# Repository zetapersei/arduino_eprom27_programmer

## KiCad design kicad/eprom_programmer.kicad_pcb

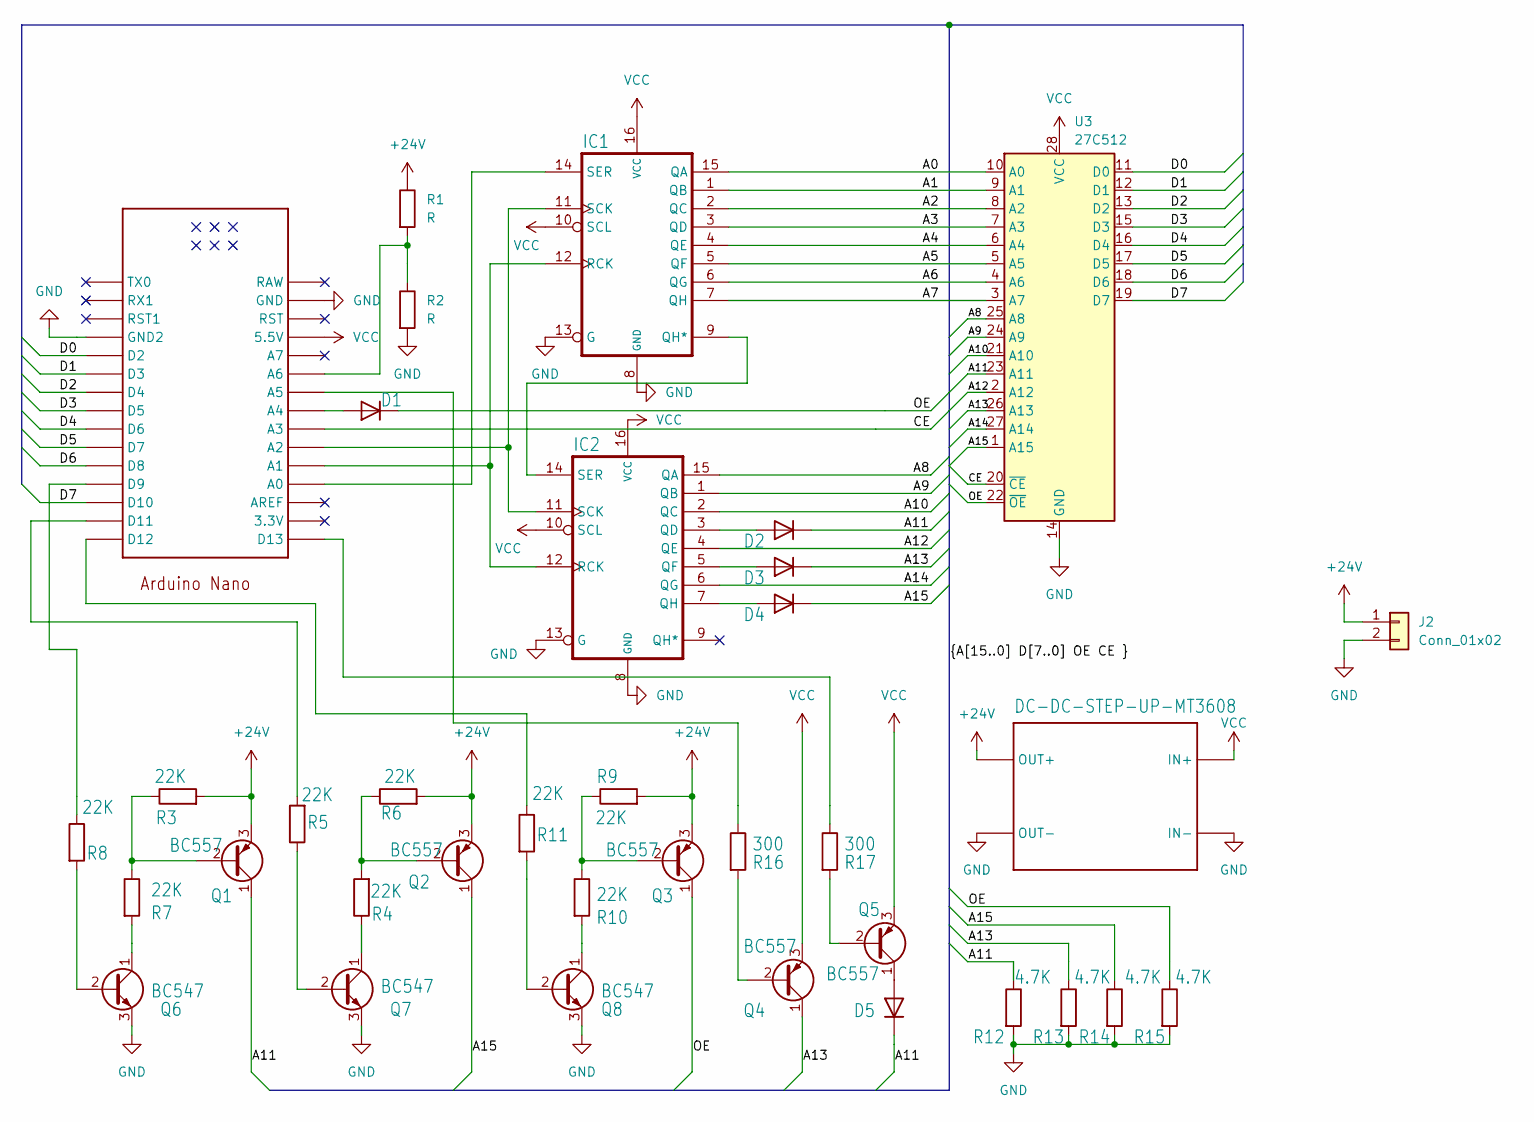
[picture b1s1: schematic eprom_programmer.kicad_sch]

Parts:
D1, D2, D3, D4, D5: 1N4148; D_DO-35_SOD27_P7.62mm_Horizontal
IC1: 74HC595D; DIP-16_W7.62mm_LongPads
IC2: 74595D; DIP-16_W7.62mm_LongPads
J2: Conn_01x02; PinHeader_1x02_P2.54mm_Vertical
Q1, Q2, Q3, Q4, Q5: BC557; TO-92_Inline
Q6, Q7, Q8: BC547; TO-92_Inline
R1, R2: R; R_Axial_DIN0207_L6.3mm_D2.5mm_P10.16mm_Horizontal
R3, R4, R5, R6, R7, R8, R9, R10, R11: 22K; R_Axial_DIN0207_L6.3mm_D2.5mm_P10.16mm_Horizontal
R12, R13, R14, R15: 4.7K; R_Axial_DIN0207_L6.3mm_D2.5mm_P10.16mm_Horizontal
R16, R17: 300; R_Axial_DIN0207_L6.3mm_D2.5mm_P10.16mm_Horizontal
U1: NANO
U2: DC-DC-STEP-UP-MT3608; MT3608
U3: 27C512; DIP_Socket-28_W11.9_W12.7_W15.24_W17.78_W18.5_3M_228-1277-0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

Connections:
+24V: J2.1, Q1.3 (E), Q2.3 (E), Q3.3 (E), R1.1, R3.2, R6.2, R9.2, U2.OUT+
/A0: IC1.15 (QA), U3.10 (A0)
/A1: IC1.1 (QB), U3.9 (A1)
/A2: IC1.2 (QC), U3.8 (A2)
/A3: IC1.3 (QD), U3.7 (A3)
/A4: IC1.4 (QE), U3.6 (A4)
/A5: IC1.5 (QF), U3.5 (A5)
/A6: IC1.6 (QG), U3.4 (A6)
/A7: IC1.7 (QH), U3.3 (A7)
/A8: IC2.15 (QA), U3.25 (A8)
/A9: IC2.1 (QB), U3.24 (A9)
/A10: IC2.2 (QC), U3.21 (A10)
/A11: D2.1 (K), D5.1 (K), Q1.1 (C), R12.1, U3.23 (A11)
/A12: IC2.4 (QE), U3.2 (A12)
/A13: D3.1 (K), Q4.1 (C), R13.1, U3.26 (A13)
/A14: IC2.6 (QG), U3.27 (A14)
/A15: D4.1 (K), Q2.1 (C), R14.1, U3.1 (A15)
/CE: U1.A3, U3.20 (~CE)
/D0: U1.D2, U3.11 (D0)
/D1: U1.D3, U3.12 (D1)
/D2: U1.D4, U3.13 (D2)
/D3: U1.D5, U3.15 (D3)
/D4: U1.D6, U3.16 (D4)
/D5: U1.D7, U3.17 (D5)
/D6: U1.D8, U3.18 (D6)
/D7: U1.D10, U3.19 (D7)
/OE: D1.1 (K), Q3.1 (C), R15.1, U3.22 (~OE)
GND: IC1.8 (GND), IC1.13 (G), IC2.8 (GND), IC2.13 (G), J2.2, Q6.3 (E), Q7.3 (E), Q8.3 (E), R2.2, R12.2, R13.2, R14.2, R15.2, U1.GND, U1.GND1 (GND2), U2.IN-, U2.OUT-, U3.14 (GND)
unnamed: D1.2 (A), U1.A4
unnamed: D2.2 (A), IC2.3 (QD)
unnamed: D3.2 (A), IC2.5 (QF)
unnamed: D4.2 (A), IC2.7 (QH)
unnamed: D5.2 (A), Q5.1 (C)
unnamed: IC1.9 (QH*), IC2.14 (SER)
unnamed: IC1.12 (RCK), IC2.12 (RCK), U1.A1
unnamed: IC1.11 (SCK), IC2.11 (SCK), U1.A2
unnamed: IC1.14 (SER), U1.A0
unnamed: Q1.2 (B), R3.1, R7.1
unnamed: Q2.2 (B), R4.2, R6.1
unnamed: Q3.2 (B), R9.1, R10.1
unnamed: Q4.2 (B), R16.2
unnamed: Q5.2 (B), R17.2
unnamed: Q6.2 (B), R8.2
unnamed: Q6.1 (C), R7.2
unnamed: Q7.2 (B), R5.1
unnamed: Q7.1 (C), R4.1
unnamed: Q8.2 (B), R11.2
unnamed: Q8.1 (C), R10.2
unnamed: R1.2, R2.1, U1.A6
unnamed: R5.2, U1.D11
unnamed: R8.1, U1.D9
unnamed: R11.1, U1.D12
unnamed: R16.1, U1.A5
unnamed: R17.1, U1.D13
VCC: IC1.10 (SCL), IC1.16 (VCC), IC2.10 (SCL), IC2.16 (VCC), Q4.3 (E), Q5.3 (E), U1.5V (5.5V), U2.IN+, U3.28 (VCC)

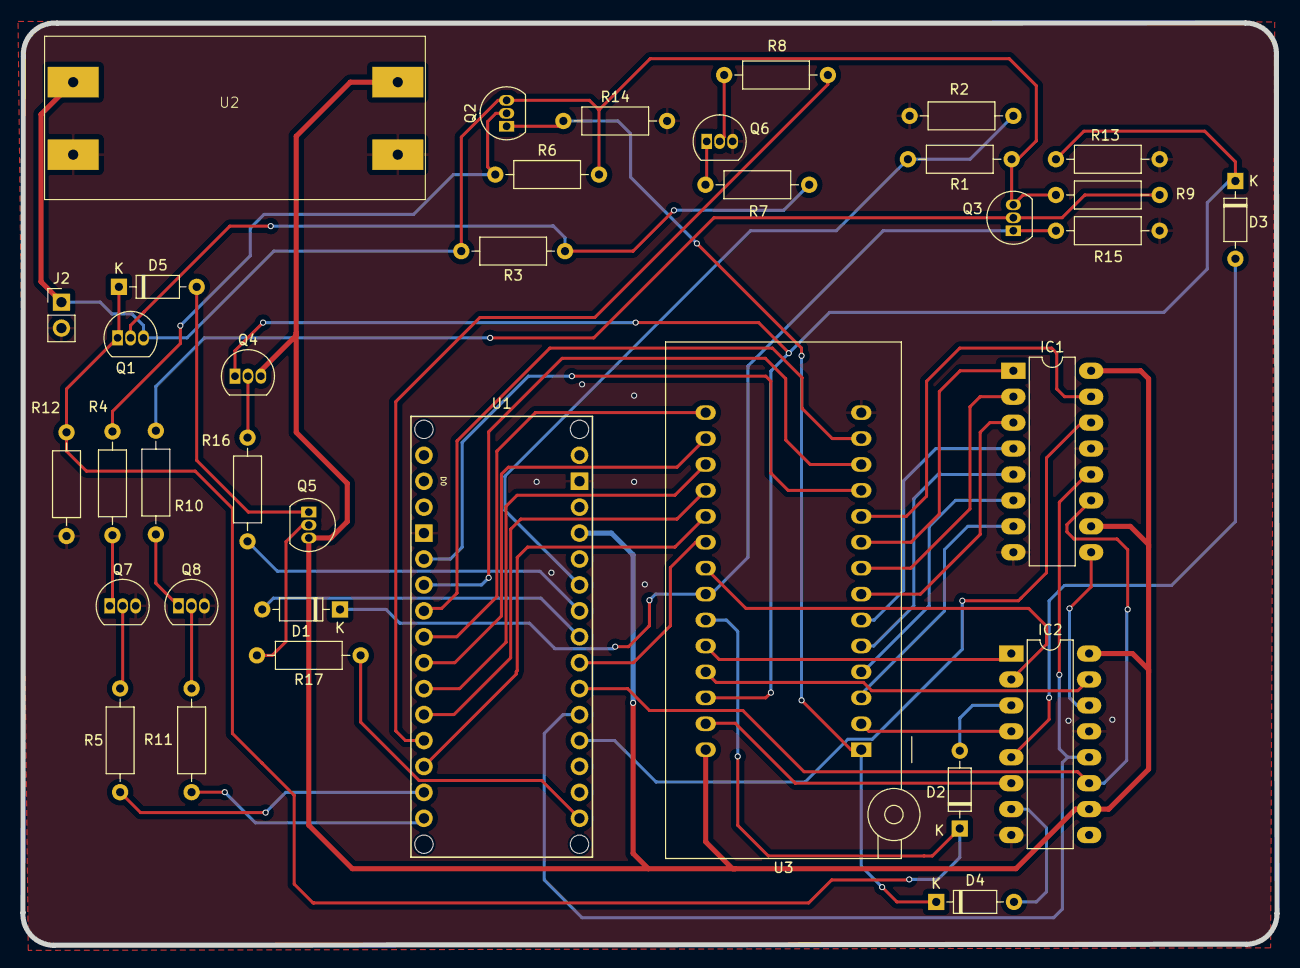
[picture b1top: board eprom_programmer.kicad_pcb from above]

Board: 2 copper layers, 122.8 x 90.3 mm, 36 parts (0 on the bottom side), 55 nets.

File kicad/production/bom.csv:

Designator,Footprint,Quantity,Value,LCSC Part #
"D1, D2, D3, D4, D5",D_DO-35_SOD27_P7.62mm_Horizontal,5,1N4148,
IC1,DIP-16_W7.62mm_LongPads,1,74HC595D,
IC2,DIP-16_W7.62mm_LongPads,1,74595D,
J2,PinHeader_1x02_P2.54mm_Vertical,1,Conn_01x02,
"Q1, Q2, Q3, Q4, Q5",TO-92_Inline,5,BC557,
"Q6, Q7, Q8",TO-92_Inline,3,BC547,
"R1, R2",R_Axial_DIN0207_L6.3mm_D2.5mm_P10.16mm_Horizontal,2,R,
"R10, R11, R3, R4, R5, R6, R7, R8, R9",R_Axial_DIN0207_L6.3mm_D2.5mm_P10.16mm_Horizontal,9,22K,
"R12, R13, R14, R15",R_Axial_DIN0207_L6.3mm_D2.5mm_P10.16mm_Horizontal,4,4.7K,
"R16, R17",R_Axial_DIN0207_L6.3mm_D2.5mm_P10.16mm_Horizontal,2,300,
U1,Arduino_Nano_Socket,1,NANO,
U2,MT3608,1,DC-DC-STEP-UP-MT3608,
U3,DIP_Socket-28_W11.9_W12.7_W15.24_W17.78_W18.5_3M_228-1277-00-0602J,1,27C512,

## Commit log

2025-01-12 modified: .gitignore new file: .vscode/extensions.json deleted: README.md deleted: eagle/untitled.brd deleted: eagle/untitled.sch deleted: gui/arduino.cpp deleted: gui/arduino.h deleted: gui/gui.pro 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
2025-01-12 new file: README.md
2025-01-12 new file: gui/arduino.cpp new file: gui/arduino.h new file: gui/gui.pro new file: gui/icon.ico new file: gui/icon.rc new file: gui/main.cpp new file: gui/mainwindow.cpp new file: gui/mainwindow.h new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
2025-01-17 new file: 27_programmer.exe new file: gui/build/Desktop_Qt_5_15_2_MinGW_32_bit-Debug/.qmake.stash new file: gui/build/Desktop_Qt_5_15_2_MinGW_32_bit-Debug/.qtc_clangd/.cache/clangd/index/QApplication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
2025-01-18 # Please enter the commit message for your change # with ' ' will be ignored, and an empty message aborts the commit. # On branch master # Your branch is up to date with 'origin/master'. # Changes to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
2025-01-18 # Please enter the commit message for your changes. Lines starting # with '# ' will be ignored, and an empty message aborts the commit.
    # On branch master
    # Your branch is up to date with 'origin/master'.
    # Changes to be committed:
    deleted: gui/build/Desktop_Qt_5_15_2_MinGW_32_bit-Debug/.qmake.stash
    deleted: gui/build/Desktop_Qt_5_15_2_MinGW_32_bit-Debug/.qtc_clangd/.cache/clangd/index/QApplication.92EED9E2DA2E5E86.idx
    deleted: gui/build/Desktop_Qt_5_15_2_MinGW_32_bit-Debug/.qtc_clangd/.cache/clangd/index/QFile.5BBB348563E3D64B.idx
